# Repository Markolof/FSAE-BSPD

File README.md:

BSPD with SCS — MES Racing
Rev 2.0 | Formula Student Rule Compliant
Brake System Plausibility Device with Short Circuit Sense. Opens the shutdown circuit if brake and motor current are simultaneously active for more than 0.5 seconds.
Key ICs

LM293 × 4 — comparators (brake & current thresholds)
NE555 — 0.5s timing
SN74HC27 — fault logic
LM358 — buffering
uA7805 — 5V regulation

Adjustable Thresholds
RV1/RV2 — brake | RV3/RV4/RV5 — current

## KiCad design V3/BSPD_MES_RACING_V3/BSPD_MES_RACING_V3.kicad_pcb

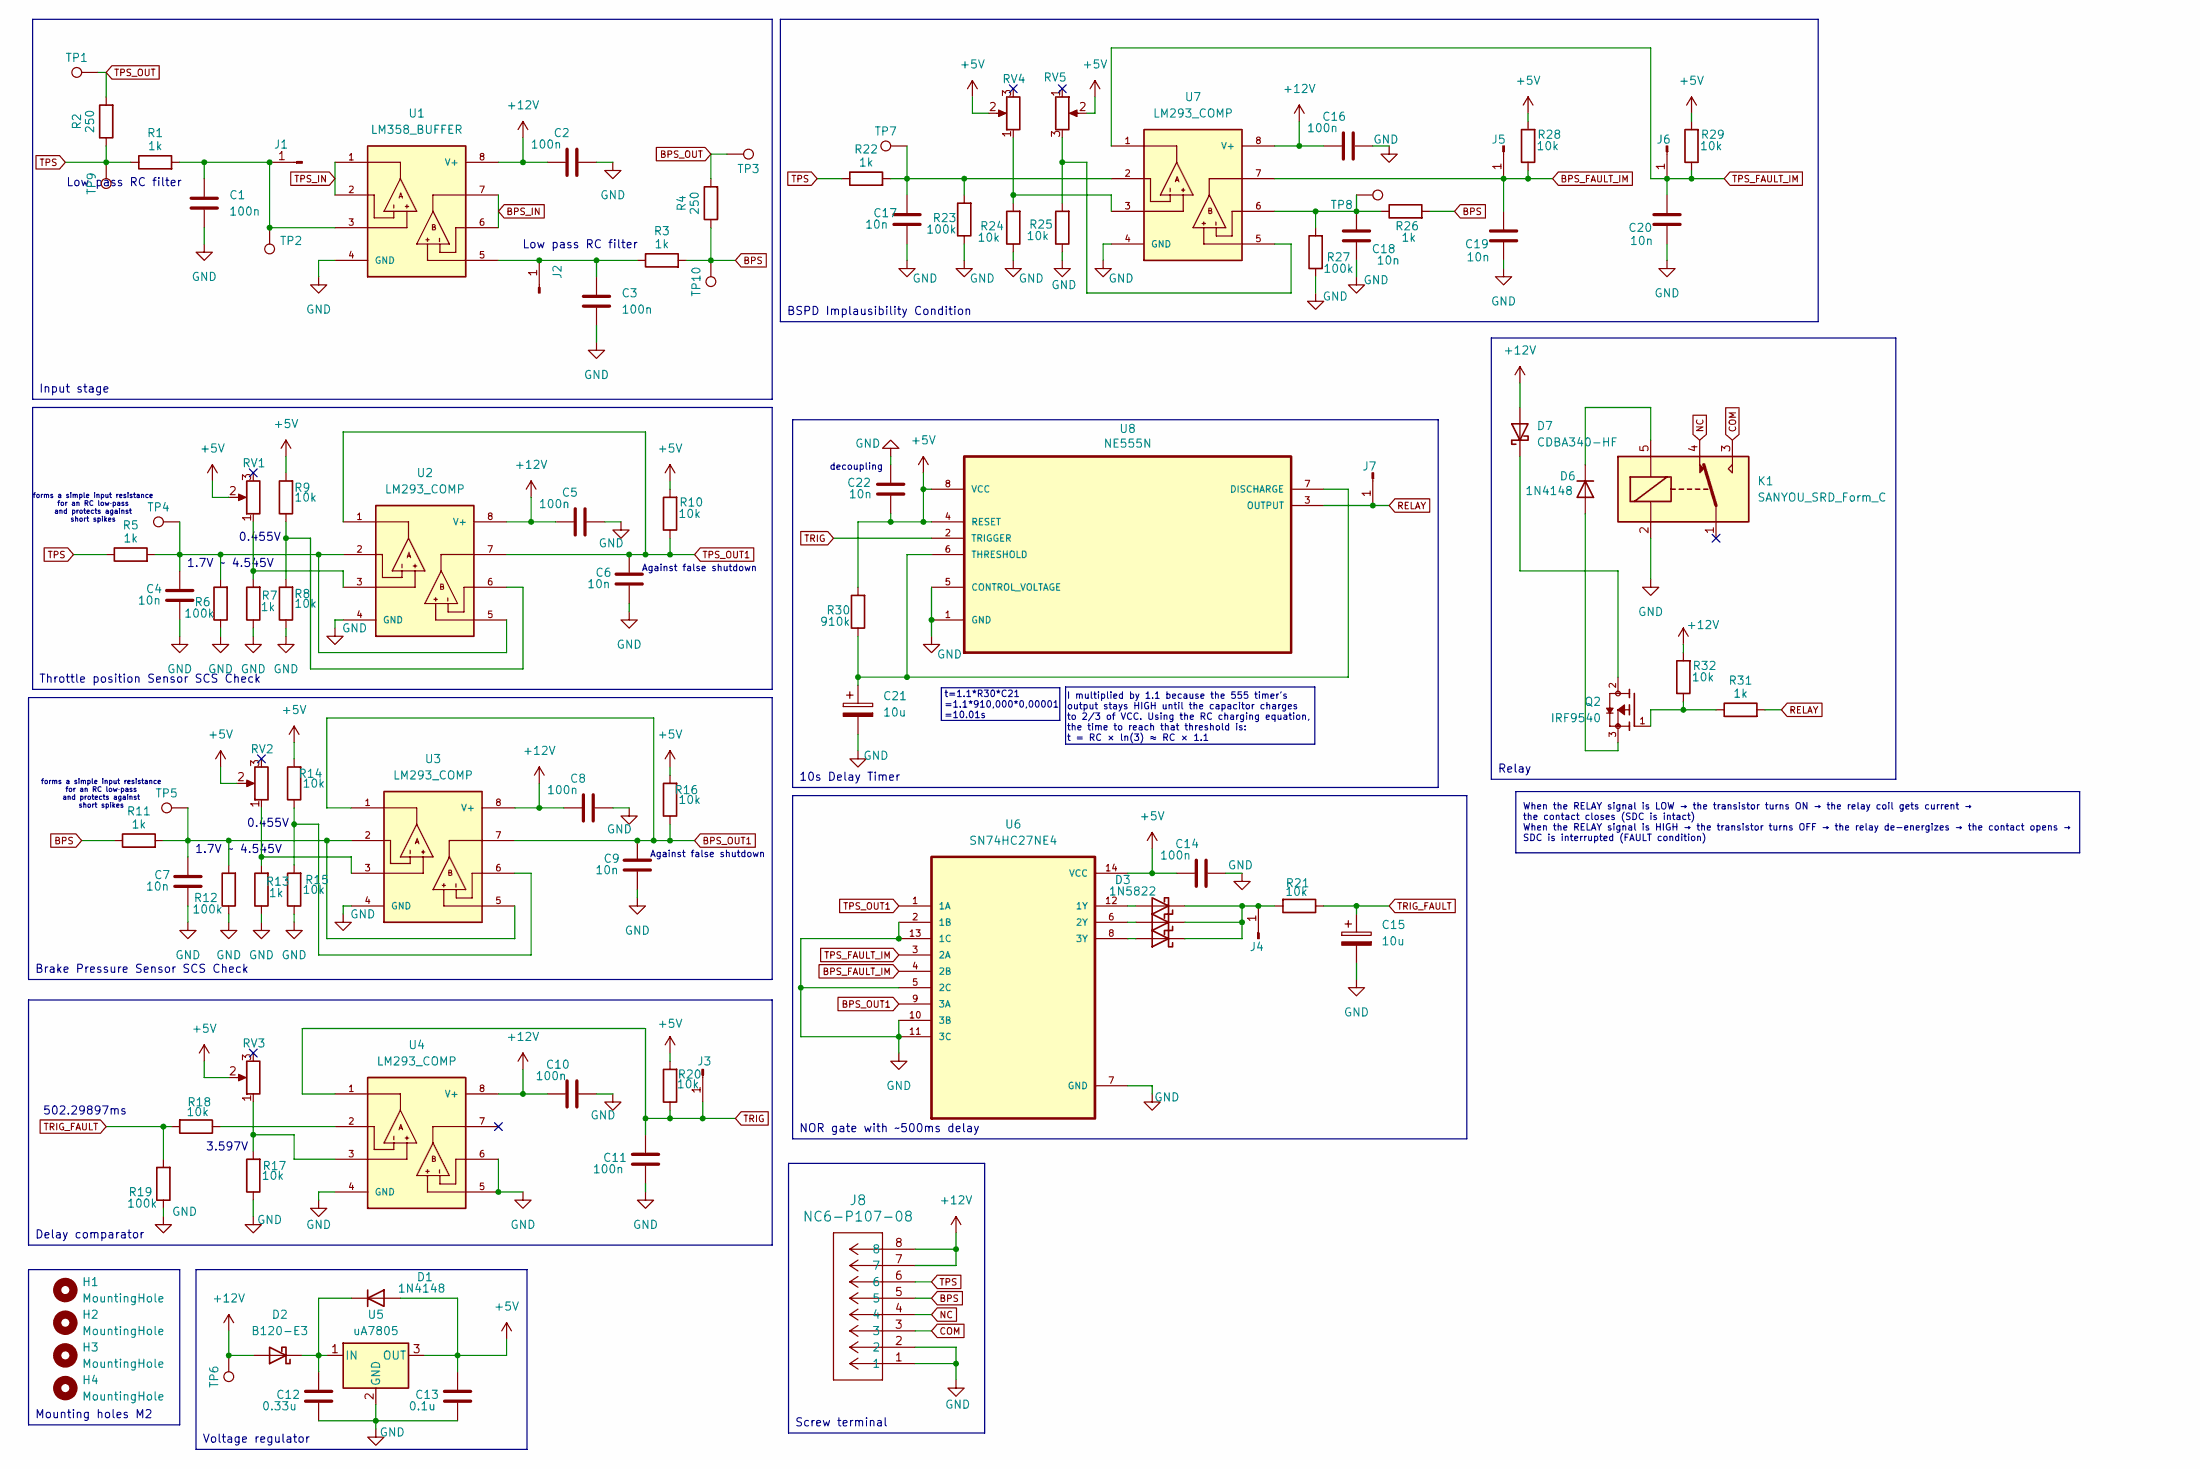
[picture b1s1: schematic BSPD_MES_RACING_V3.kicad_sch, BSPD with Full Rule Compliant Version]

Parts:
C1, C2, C3, C5, C8, C10, C11, C14, C16: 100n; Resonator-2Pin_W7.0mm_H2.5mm
C4, C6, C7, C9, C17, C18, C19, C20, C22: 10n; Resonator-2Pin_W7.0mm_H2.5mm
C12: 0.33u; Resonator-2Pin_W7.0mm_H2.5mm
C13: 0.1u; Resonator-2Pin_W7.0mm_H2.5mm
C15, C21: 10u; CP_Radial_D8.0mm_P5.00mm
D1, D6: 1N4148; D_DO-35_SOD27_P7.62mm_Horizontal
D2: B120-E3; D_DO-201AE_P15.24mm_Horizontal
D3, D4, D5: 1N5822; D_DO-201AD_P15.24mm_Horizontal
D7: CDBA340-HF; D_DO-201AE_P15.24mm_Horizontal
H1, H2, H3, H4: MountingHole; MountingHole_2.2mm_M2
J1, J2, J3, J4, J5, J6, J7: Conn_01x01_Pin; PinHeader_1x01_P2.54mm_Vertical
J8: NC6-P107-08; CONN8_NC6-P107-08_TEC
K1: SANYOU_SRD_Form_C; Relay_SPDT_SANYOU_SRD_Series_Form_C
Q2: IRF9540; TO254P1052X465X1989-3; PARTREV B
R1, R3, R5, R7, R11, R13, R22, R26, R31: 1k; R_Axial_DIN0207_L6.3mm_D2.5mm_P10.16mm_Horizontal
R2, R4: 250; R_Axial_DIN0207_L6.3mm_D2.5mm_P10.16mm_Horizontal
R6, R12, R19, R23, R27: 100k; R_Axial_DIN0207_L6.3mm_D2.5mm_P10.16mm_Horizontal
R8, R9, R10, R14, R15, R16, R17, R18, R20, R21, R24, R25, R28, R29, R32: 10k; R_Axial_DIN0207_L6.3mm_D2.5mm_P10.16mm_Horizontal
R30: 910k; R_Axial_DIN0207_L6.3mm_D2.5mm_P10.16mm_Horizontal
RV1, RV2, RV3, RV4, RV5: 100k; Potentiometer_Bourns_3266Y_Vertical
TP1, TP2, TP3, TP4, TP5, TP6, TP7, TP8, TP9, TP10: TestPoint; TestPoint_Pad_4.0x4.0mm
U1: LM358_BUFFER; DIP794W45P254L959H508Q8
U2, U3, U4, U7: LM293_COMP; DIP794W45P254L959H508Q8
U5: uA7805; TO-220-3_Horizontal_TabDown
U6: SN74HC27NE4; CERDIP-14_W7.62mm_SideBrazed_LongPads_Socket
U8: NE555N; CERDIP-8_W7.62mm_SideBrazed_LongPads_Socket; MPN NE555N

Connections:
+5V: C13.2, C14.1, C22.2, D1.2 (A), R9.2, R10.2, R14.2, R16.2, R20.2, R28.2, R29.2, R30.2, RV1.2, RV2.2, RV3.2, RV4.2, RV5.2, U5.3 (OUT), U6.14 (VCC), U8.4 (RESET), U8.8 (VCC)
+12V: C2.1, C5.1, C8.1, C10.1, C16.1, D2.2 (A), D7.2 (A), J8.7, J8.8, R32.2, TP6.1, U1.8 (V+), U2.8 (V+), U3.8 (V+), U4.8 (V+), U7.8 (V+)
BPS: J8.5, R3.2, R4.1, R11.1, R26.2, TP10.1
BPS_FAULT_IM: C19.1, J5.1, R28.1, U6.4 (2B), U7.7
BPS_IN: U1.6, U1.7
BPS_OUT: R4.2, TP3.1
BPS_OUT1: C9.1, R16.1, U3.1, U3.7, U6.9 (3A)
COM: J8.3, K1.3
GND: C1.2, C2.2, C3.2, C4.2, C5.2, C6.2, C7.2, C8.2, C9.2, C10.2, C11.1, C12.1, C13.1, C14.2, C15.2, C16.2, C17.2, C18.2, C19.2, C20.2, C21.2, C22.1, J8.1, J8.2, K1.2, R6.1, R7.1, R8.1, R12.1, R13.1, R15.1, R17.1, R19.1, R23.1, R24.1, R25.1, R27.1, U1.4 (GND), U2.4 (GND), U3.4 (GND), U4.4 (GND), U4.5, U4.6, U5.2 (GND), U6.2 (1B), U6.5 (2C), U6.7 (GND), U6.10 (3B), U6.11 (3C), U6.13 (1C), U7.4 (GND), U8.1 (GND), U8.5 (CONTROL_VOLTAGE)
NC: J8.4, K1.4
unnamed: C4.1, R5.2, R6.2, TP4.1, U2.2, U2.5
unnamed: C7.1, R11.2, R12.2, TP5.1, U3.2, U3.5
unnamed: C17.1, R22.2, R23.2, TP7.1, U7.2
unnamed: C18.1, R26.1, R27.2, TP8.1, U7.6
unnamed: C12.2, D1.1 (K), D2.1 (K), U5.1 (IN)
unnamed: D3.2 (A), U6.12 (1Y)
unnamed: D3.1 (K), D4.1 (K), D5.1 (K), J4.1, R21.2
unnamed: D4.2 (A), U6.6 (2Y)
unnamed: D5.2 (A), U6.8 (3Y)
unnamed: D6.2 (A), Q2.3
unnamed: D6.1 (K), K1.5
unnamed: D7.1 (K), Q2.2
unnamed: C1.1, J1.1, R1.2, TP2.1, U1.3
unnamed: C3.1, J2.1, R3.1, U1.5
unnamed: Q2.1, R31.1, R32.1
unnamed: R7.2, RV1.1, U2.3
unnamed: R8.2, R9.1, U2.6
unnamed: R13.2, RV2.1, U3.3
unnamed: R14.1, R15.2, U3.6
unnamed: R17.2, RV3.1, U4.3
unnamed: R18.1, U4.2
unnamed: R24.2, RV4.1, U7.3
unnamed: R25.2, RV5.3, U7.5
unnamed: C21.1, R30.1, U8.6 (THRESHOLD), U8.7 (DISCHARGE)
RELAY: J7.1, R31.2, U8.3 (OUTPUT)
TPS: J8.6, R1.1, R2.1, R5.1, R22.1, TP9.1
TPS_FAULT_IM: C20.1, J6.1, R29.1, U6.3 (2A), U7.1
TPS_IN: U1.1, U1.2
TPS_OUT: R2.2, TP1.1
TPS_OUT1: C6.1, R10.1, U2.1, U2.7, U6.1 (1A)
TRIG: C11.2, J3.1, R20.1, U4.1, U8.2 (TRIGGER)
TRIG_FAULT: C15.1, R18.2, R19.2, R21.1

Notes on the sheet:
3.597V
When the RELAY signal is LOW → the transistor turns ON → the relay coil gets current → the contact closes (SDC is intact) When the RELAY signal is HIGH → the transistor turns OFF → the relay de-energizes → the contact opens → SDC is interrupted (FAULT condition)
forms a simple input resistance for an RC low‑pass and protects against short spikes
502.29897ms
0.455V
Low pass RC filter
I multiplied by 1.1 because the 555 timer's output stays HIGH until the capacitor charges to 2/3 of VCC. Using the RC charging equation, the time to reach that threshold is: t = RC × ln(3) ≈ RC × 1.1
Against false shutdown
t=1.1*R30*C21 =1.1*910,000*0,00001 =10.01s
1.7V ~ 4.545V
decoupling
Relay
NOR gate with ~500ms delay
Screw terminal
Brake Pressure Sensor SCS Check
Throttle position Sensor SCS Check
Input stage
10s Delay Timer
BSPD Implausibility Condition
Voltage regulator
Mounting holes M2
Delay comparator

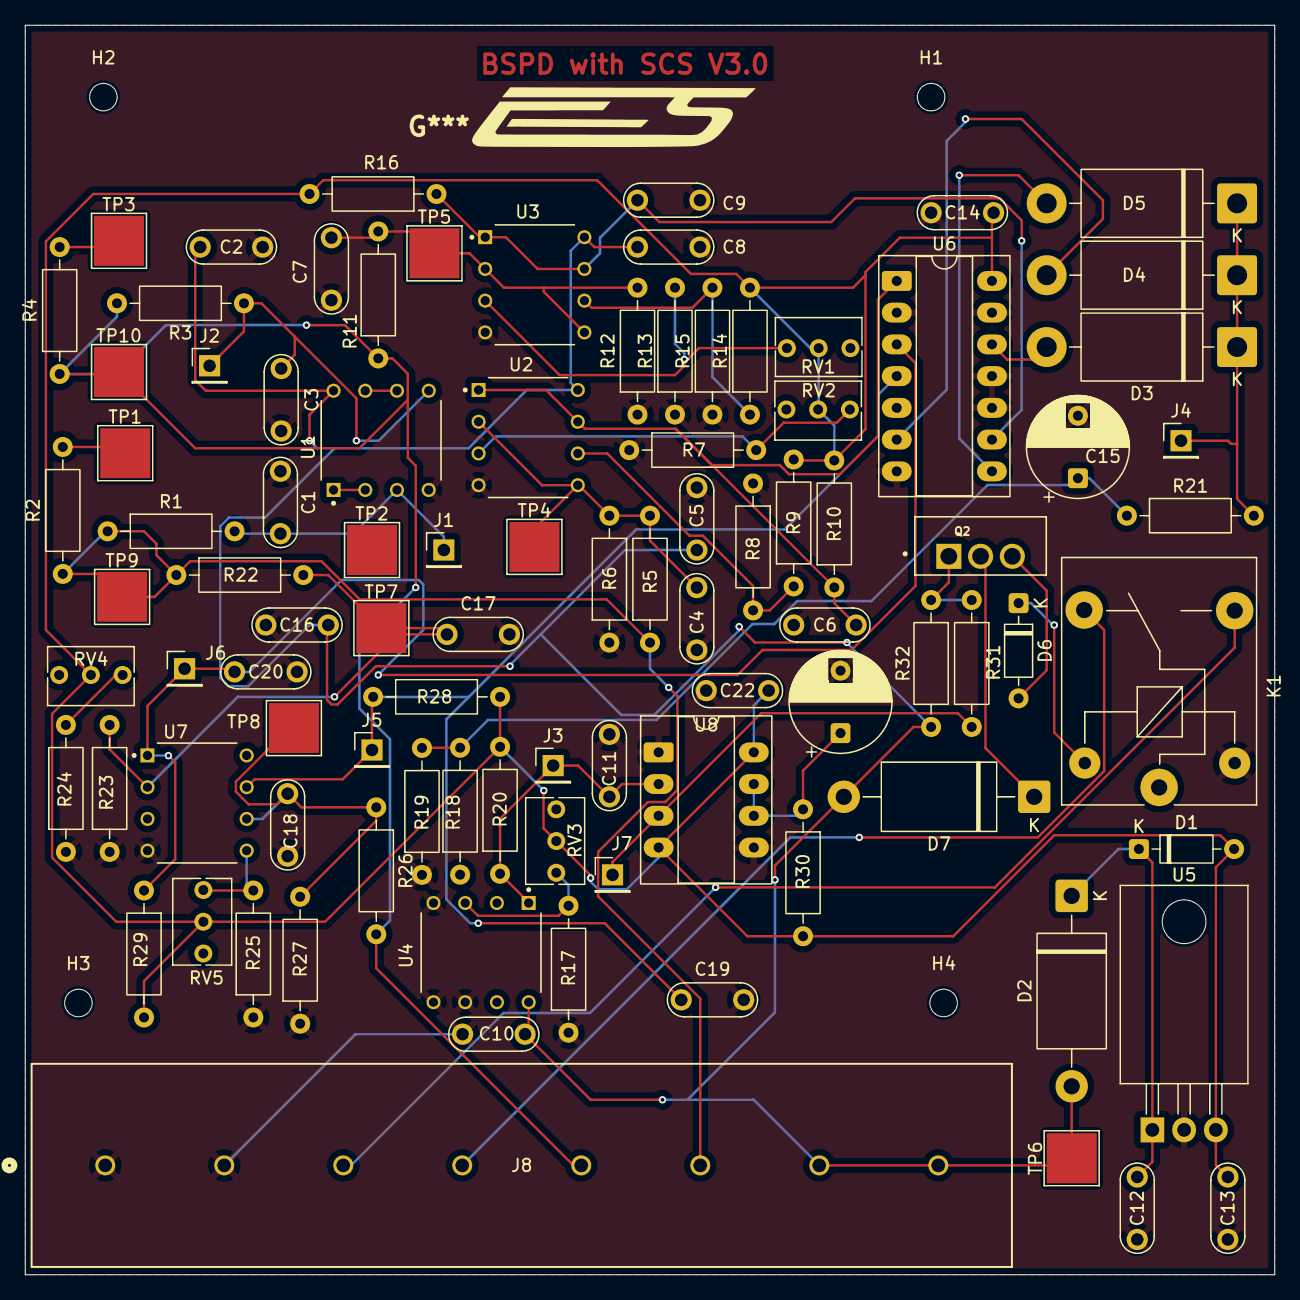
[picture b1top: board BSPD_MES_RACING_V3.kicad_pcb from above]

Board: 2 copper layers, 100.0 x 100.0 mm, 98 parts (0 on the bottom side), 42 nets.

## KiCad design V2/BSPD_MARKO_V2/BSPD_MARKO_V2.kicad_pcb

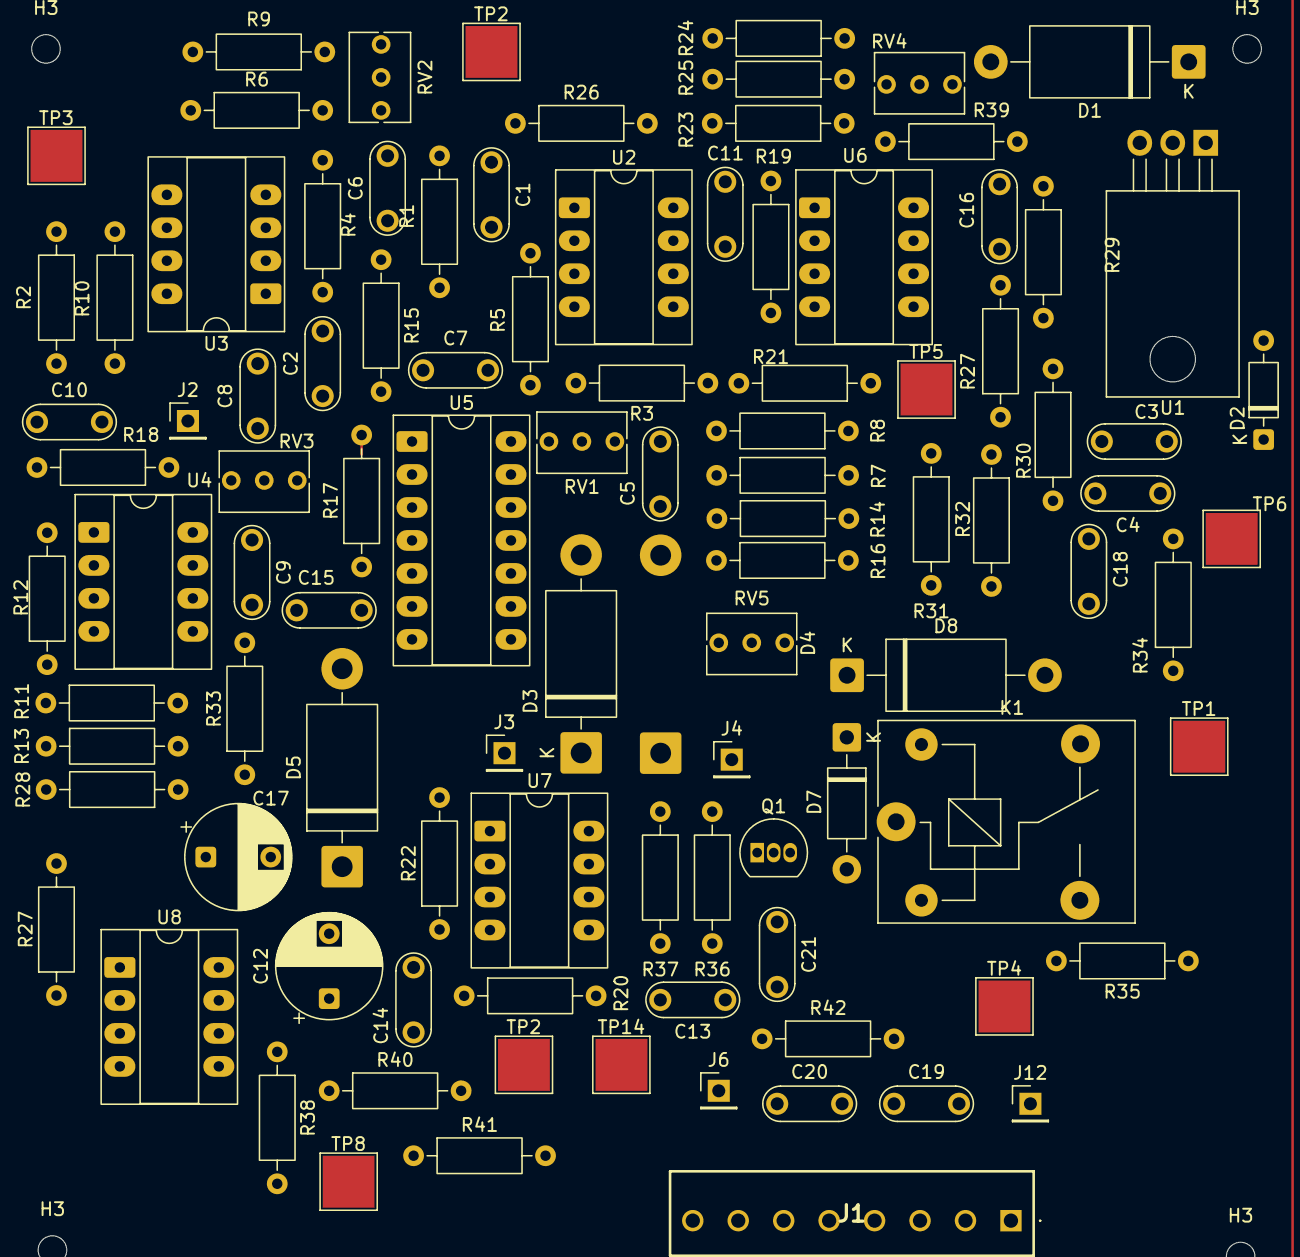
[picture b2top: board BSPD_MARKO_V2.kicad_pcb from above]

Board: 2 copper layers, 105 parts (1 on the bottom side), 43 nets.

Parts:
C1, C2, C11, C14, C18: 10n; Resonator-2Pin_W7.0mm_H2.5mm
C3: 0.33u; Resonator-2Pin_W7.0mm_H2.5mm
C4: 0.1u; Resonator-2Pin_W7.0mm_H2.5mm
C5, C6, C9, C13, C15, C16, C19, C20, C21: 100n; Resonator-2Pin_W7.0mm_H2.5mm
C7, C8: 15p; Resonator-2Pin_W7.0mm_H2.5mm
C10: 15u; Resonator-2Pin_W7.0mm_H2.5mm
C12, C17: 10u; CP_Radial_D8.0mm_P5.00mm
D1: B120-E3; D_DO-201AE_P15.24mm_Horizontal
D2: 1N4148; D_DO-35_SOD27_P7.62mm_Horizontal
D3, D4, D5: 1N5822; D_DO-201AD_P15.24mm_Horizontal
D7: 1N4007; D_DO-41_SOD81_P10.16mm_Horizontal
D8: CDBA340-HF; D_DO-201AE_P15.24mm_Horizontal
H3, H3#2, H3#3, H3#4: MountingHole; MountingHole_2.2mm_M2
J1: ED555_8DS; ED5558DS
J2: 01x01P; PinHeader_1x01_P2.54mm_Vertical
J3, J4: Conn_01x01_Pin; PinHeader_1x01_P2.54mm_Vertical
J6, J12: 01x01_Pin; PinHeader_1x01_P2.54mm_Vertical
K1: SANYOU_SRD_Form_C; Relay_SPDT_SANYOU_SRD_Series_Form_C
Q1: 2N3904; TO-92_Inline
R1, R2, R19, R27#2, R34, R38, R39, R42: 1k; R_Axial_DIN0207_L6.3mm_D2.5mm_P10.16mm_Horizontal
R3, R4, R7, R9, R11, R16, R17, R21, R22, R24, R26, R27, R29, R30: 100k; R_Axial_DIN0207_L6.3mm_D2.5mm_P10.16mm_Horizontal
R5, R6, R23, R31: 51k; R_Axial_DIN0207_L6.3mm_D2.5mm_P10.16mm_Horizontal
R8, R10, R12, R13, R14, R15, R18, R25, R28, R32, R33, R35, R36, R37: 10k; R_Axial_DIN0207_L6.3mm_D2.5mm_P10.16mm_Horizontal
R20: 910k; R_Axial_DIN0207_L6.3mm_D2.5mm_P10.16mm_Horizontal
R40, R41: 250; R_Axial_DIN0207_L6.3mm_D2.5mm_P10.16mm_Horizontal
RV1, RV2, RV3, RV4, RV5: 100k; Potentiometer_Bourns_3266Y_Vertical
TP1, TP2, TP2#2, TP3, TP4, TP6, TP8, TP14: TestPoint; TestPoint_Pad_4.0x4.0mm
TP5: TP; TestPoint_Pad_4.0x4.0mm
U1: uA7805; TO-220-3_Horizontal_TabDown
U2, U3, U4, U6, U8: LM293_COMP; CERDIP-8_W7.62mm_SideBrazed_LongPads_Socket
U5: SN74HC27NE4; CERDIP-14_W7.62mm_SideBrazed_LongPads_Socket
U7: NE555N; CERDIP-8_W7.62mm_SideBrazed_LongPads_Socket

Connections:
+5V: C4.1, C13.2, C15.1, D2.2 (A), R7.1, R9.1, R14.1, R15.1, R18.1, R20.1, R22.1, R24.1, R27#2.1, R29.1, R33.2, R39.1, RV1.2, RV2.2, RV3.2, RV4.2, RV5.2, U1.3 (OUT), U5.14 (VCC), U7.4 (RESET), U7.8 (VCC)
BPS: J1.5, R1.2, R34.1, R40.1, R42.2
BPS1_OUT: C7.1, R14.2, R16.2, U2.1, U2.7, U5.1 (1A)
BPS_IN: U8.6, U8.7
BSPD_BPS_F: R27#2.2, U5.4 (2B), U6.7
BSPD_TPS_F: R26.2, R39.2, U5.3 (2A), U6.1
GND: C1.2, C2.2, C3.2, C4.2, C5.2, C6.2, C7.2, C8.2, C9.2, C10.2, C11.2, C12.2, C13.1, C14.1, C15.2, C16.2, C17.2, C18.2, C19.1, C20.2, C21.1, J1.1, J1.2, Q1.1 (E), R3.2, R4.2, R5.2, R6.2, R8.2, R10.2, R11.2, R13.2, R21.2, R23.2, R25.2, R30.2, R31.2, R32.2, R36.1, TP4.1, U1.2 (GND), U2.4 (GND), U3.4 (GND), U4.4 (GND), U4.5, U4.6, U5.2 (1B), U5.5 (2C), U5.7 (GND), U5.10 (3B), U5.11 (3C), U5.13 (1C), U6.4 (GND), U7.1 (GND), U8.4 (GND)
NO: C5.1, C6.1, C9.1, C16.1, C20.1, D1.2 (A), D8.2 (A), J1.4, J1.7, J1.8, K1.4, TP1.1, U2.8 (V+), U3.8 (V+), U4.8 (V+), U6.8 (V+), U8.8 (V+)
unnamed: C1.1, R1.1, R3.1, TP2#2.1, U2.2, U2.5
unnamed: C2.1, R2.1, R4.1, TP3.1, U3.2, U3.5
unnamed: C11.1, R19.1, R21.1, R26.1, TP5.1, U6.3
unnamed: C18.1, R27.1, R32.1, R34.2, TP6.1, U6.5
unnamed: C3.1, D1.1 (K), D2.1 (K), U1.1 (IN)
unnamed: D3.2 (A), U5.8 (3Y)
unnamed: D3.1 (K), D4.1 (K), D5.1 (K), J3.1, R28.1
unnamed: D4.2 (A), U5.12 (1Y)
unnamed: D5.2 (A), U5.6 (2Y)
unnamed: D7.2 (A), K1.2, R35.2
unnamed: D7.1 (K), D8.1 (K), K1.5
unnamed: C21.2, J6.1, R42.1, U8.5
unnamed: C19.2, J12.1, R38.2, TP8.1, U8.3
unnamed: R36.2, R37.2
unnamed: R7.2, R8.1, U2.6
unnamed: R9.2, R10.1, U3.6
unnamed: R12.2, U4.2
unnamed: R13.1, RV3.1, U4.3
unnamed: R5.1, R16.1, RV1.1, U2.3
unnamed: R6.1, R17.1, RV2.1, U3.3
unnamed: R23.1, RV4.1, U6.2
unnamed: R24.2, R25.1
unnamed: R29.2, R30.1
unnamed: R31.1, RV5.1, U6.6
unnamed: R40.2, TP2.1
unnamed: C14.2, U7.5 (CONTROL_VOLTAGE)
unnamed: C12.1, R20.2, U7.6 (THRESHOLD), U7.7 (DISCHARGE)
Rel: J4.1, R37.1, U7.3 (OUTPUT)
SC: J1.3, K1.1
TPS: J1.6, R2.2, R19.2, R38.1, R41.1
TPS1_OUT: C8.1, R15.2, R17.2, U3.1, U3.7, U5.9 (3A)
TPS_IN: U8.1, U8.2
TPS_OUT: R41.2, TP14.1
Trig: C10.1, J2.1, R18.2, U4.1
Trig_Fault: C17.1, Q1.3 (C), R11.1, R12.1, R22.2, R28.2, R33.1, U7.2 (TRIGGER)

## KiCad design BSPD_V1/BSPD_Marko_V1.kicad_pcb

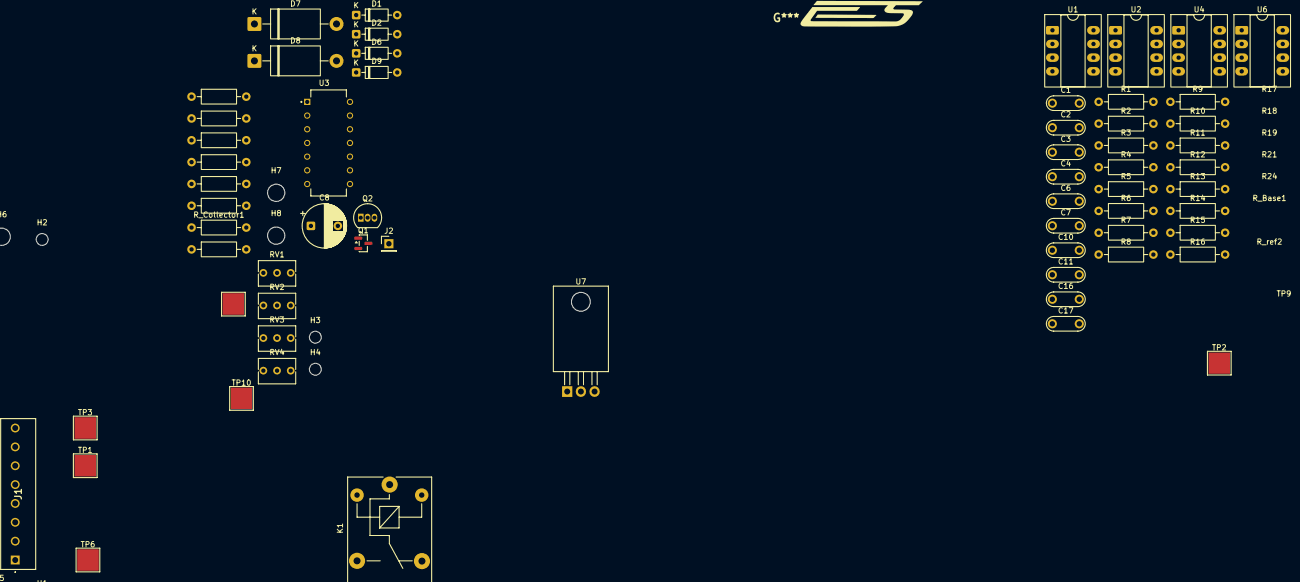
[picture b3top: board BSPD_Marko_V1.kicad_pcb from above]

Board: 2 copper layers, 70 parts (0 on the bottom side), 29 nets, no tracks yet.

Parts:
C1, C2, C3, C4, C6: 100n; Resonator-2Pin_W7.0mm_H2.5mm
C7: 10n; Resonator-2Pin_W7.0mm_H2.5mm
C8: 10u; CP_Radial_D8.0mm_P5.00mm
C10: 0.1u; Resonator-2Pin_W7.0mm_H2.5mm
C11: 0.33u; Resonator-2Pin_W7.0mm_H2.5mm
C16, C17: 15p; Resonator-2Pin_W7.0mm_H2.5mm
D1, D2, D6, D9: 1N4148; D_DO-35_SOD27_P7.62mm_Horizontal
D7: CDBA340-HF; D_DO-201AE_P15.24mm_Horizontal
D8: B120-E3; D_DO-201AE_P15.24mm_Horizontal
H1, H2, H3, H4: MountingHole; MountingHole_2.2mm_M2
H5, H6, H7, H8: MountingHole; MountingHole_3.2mm_M3
J1: ED555_8DS; ED5558DS
J2: Conn_01x01_Pin; PinHeader_1x01_P2.54mm_Vertical
K1: SANYOU_SRD_Form_C; Relay_SPDT_SANYOU_SRD_Series_Form_C
Q1: BSS83P; SOT-23
Q2: 2N3904; TO-92_Inline
R1, R2, R3, R6, R11, R13, R16: 10k; R_Axial_DIN0207_L6.3mm_D2.5mm_P10.16mm_Horizontal
R4, R8, R9, R15: 1k; R_Axial_DIN0207_L6.3mm_D2.5mm_P10.16mm_Horizontal
R5, R7, R10, R12, R14, R17, R18, R19, R24: 100k; R_Axial_DIN0207_L6.3mm_D2.5mm_P10.16mm_Horizontal
R21: 910k; R_Axial_DIN0207_L6.3mm_D2.5mm_P10.16mm_Horizontal
RV1, RV2, RV3, RV4: 10k; Potentiometer_Bourns_3266Y_Vertical
R_Base1: 10k; R_Axial_DIN0207_L6.3mm_D2.5mm_P10.16mm_Horizontal
R_Collector1: 10k; R_Axial_DIN0207_L6.3mm_D2.5mm_P10.16mm_Horizontal
R_ref2: 10k; R_Axial_DIN0207_L6.3mm_D2.5mm_P10.16mm_Horizontal
TP1, TP2, TP3, TP6, TP9, TP10: TestPoint; TestPoint_Pad_4.0x4.0mm
U1, U2, U4: LM293_COMP; CERDIP-8_W7.62mm_SideBrazed_LongPads_Socket
U3: SN74HC08N; DIP794W45P254L1969H508Q14
U6: NE555N; CERDIP-8_W7.62mm_SideBrazed_LongPads_Socket
U7: uA7805; TO-220-3_Horizontal_TabDown

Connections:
+5V: C3.1, C6.1, C10.1, D9.2 (A), Q1.2 (S), R2.2, R3.2, R5.2, R10.2, R12.2, R19.2, R21.1, R24.1, RV1.2, RV2.2, RV3.2, RV4.2, R_Collector1.2, U3.14 (VCC), U6.4 (RESET), U6.8 (VCC), U7.3 (OUT)
+12V: C1.1, C2.1, C4.1, D7.2 (A), D8.2 (A), J1.7, J1.8, R_ref2.2, TP3.1, U1.8 (V+), U2.8 (V+), U4.8 (V+)
BPS: J1.5, R16.2, R18.2, TP2.1, TP10.1, U2.2, U2.5, U4.6
BPS_OUT: C17.2, R2.1, U2.1, U2.7, U3.2 (1B)
BSPD_F: D1.1 (K), D2.1 (K), U3.4 (2A)
GND: C1.2, C2.2, C3.2, C4.2, C6.2, C7.1, C8.2, C10.2, C11.2, C16.1, C17.1, J1.1, J1.2, Q2.1 (E), R1.1, R4.1, R6.1, R7.1, R8.1, R9.1, R11.1, R13.1, R14.1, R15.1, R16.1, R17.1, R18.1, TP6.1, U1.4 (GND), U2.4 (GND), U3.5 (2B), U3.7 (GND), U3.9 (3A), U3.10 (3B), U3.12 (4A), U3.13 (4B), U4.4 (GND), U6.1 (GND), U7.2 (GND)
NO: J1.4, K1.4, R_ref2.1
unnamed: D1.2 (A), U4.1
unnamed: D2.2 (A), U4.7
unnamed: D6.2 (A), K1.2, Q1.3 (D)
unnamed: D6.1 (K), D7.1 (K), K1.5
unnamed: C11.1, D8.1 (K), D9.1 (K), U7.1 (IN)
unnamed: Q2.2 (B), R_Base1.2
unnamed: R4.2, RV1.1, U1.3
unnamed: R5.1, R6.2, U1.6
unnamed: R8.2, RV3.1, U4.3
unnamed: R9.2, RV2.1, U2.3
unnamed: R10.1, R11.2, U2.6
unnamed: R12.1, R13.2
unnamed: R14.2, R19.1
unnamed: R15.2, RV4.3, U4.5
unnamed: R_Base1.1, U3.3 (1Y)
unnamed: C7.2, U6.5 (CONTROL_VOLTAGE)
unnamed: C8.1, R21.2, U6.6 (THRESHOLD), U6.7 (DISCHARGE)
Rel: J2.1, U6.3 (OUTPUT)
SC: J1.3, K1.1
TPS: J1.6, R7.2, R17.2, TP1.1, TP9.1, U1.2, U1.5, U4.2
TPS_OUT: C16.2, R3.1, U1.1, U1.7, U3.1 (1A)
Trig_Fault: Q1.1 (G), Q2.3 (C), R1.2, R24.2, R_Collector1.1, U6.2 (TRIGGER)
